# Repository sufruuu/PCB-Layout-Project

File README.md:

# PCB-Layout-Project
Submitted by T S Subramaniyan  
Final project submission on Schematic &amp; PCB Layout Designing.  
## Square Wave Generator using NE555 IC
Requirements:
- frequenchy = 1kHz
- Duty CYcle = 50%
- IC = NE555
- Used **Proteus** for circuit simulation
- Used **KiCAD V8.0.6** for Schematic Design and Layout Designing

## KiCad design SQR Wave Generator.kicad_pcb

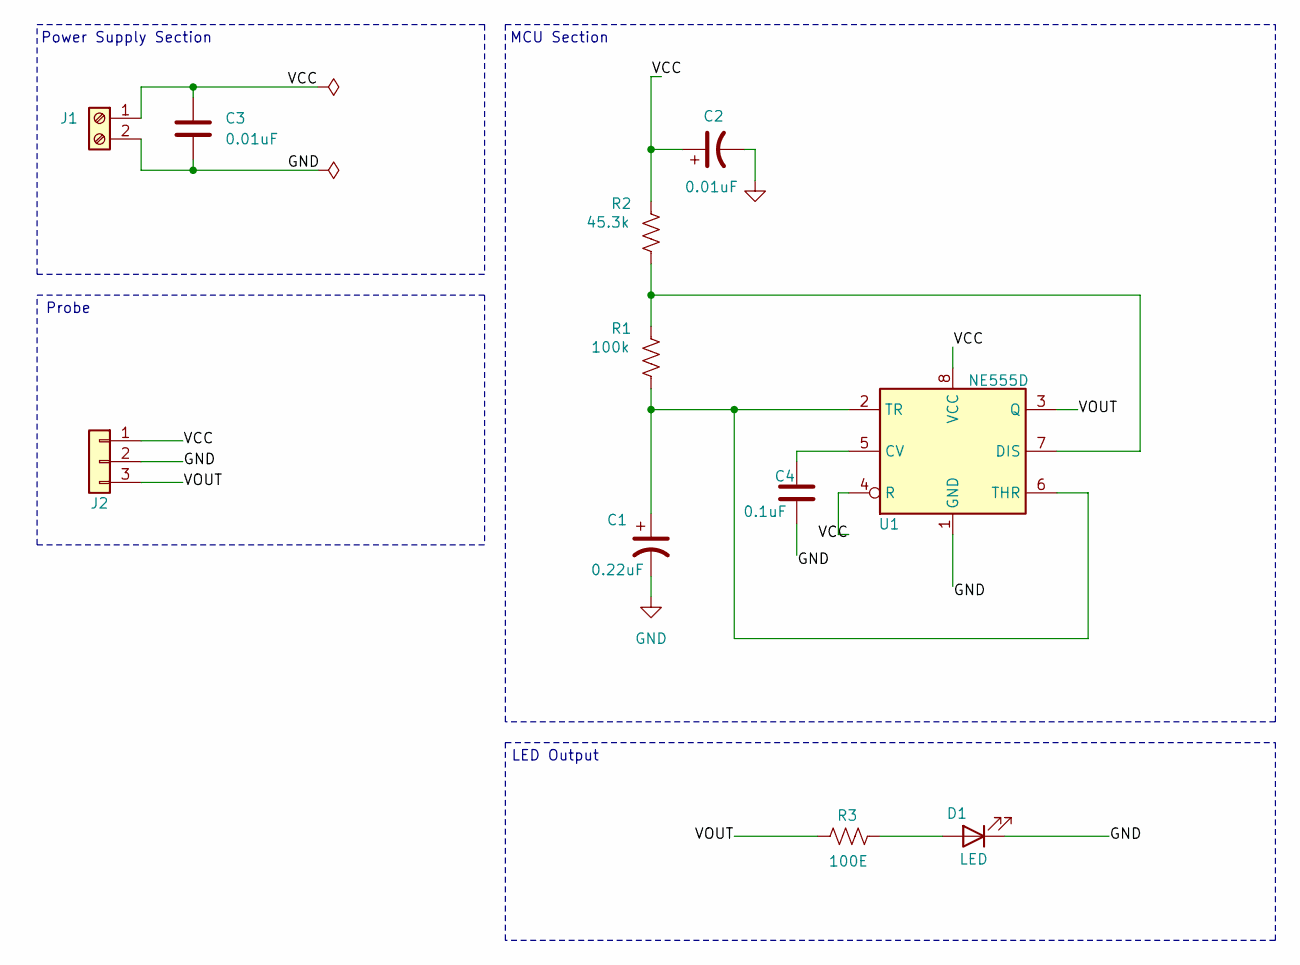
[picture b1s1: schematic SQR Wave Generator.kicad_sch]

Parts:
C1: 0.22uF; C_0805_2012Metric_Pad1.18x1.45mm_HandSolder
C2, C3: 0.01uF; C_0805_2012Metric_Pad1.18x1.45mm_HandSolder
C4: 0.1uF; C_0805_2012Metric_Pad1.18x1.45mm_HandSolder
D1: LED; LED_0805_2012Metric
J1: Screw_Terminal_01x02; TerminalBlock_Phoenix_MKDS-1,5-2-5.08_1x02_P5.08mm_Horizont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
J2: Conn_01x02; PinHeader_1x03_P2.54mm_Vertical
R1: 100k; R_0805_2012Metric
R2: 45.3k; R_0805_2012Metric
R3: 100E; R_0805_2012Metric
U1: NE555D; SOIC-8_3.9x4.9mm_P1.27mm

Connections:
/VCC: C2.1, C3.1, J1.1, J2.1, R2.1, U1.4 (R), U1.8 (VCC)
/VOUT: J2.3, R3.1, U1.3 (Q)
GND: C1.2, C2.2, C3.2, C4.2, D1.1 (K), J1.2, J2.2, U1.1 (GND)
unnamed: D1.2 (A), R3.2
unnamed: C4.1, U1.5 (CV)
unnamed: R1.1, R2.2, U1.7 (DIS)
unnamed: C1.1, R1.2, U1.2 (TR), U1.6 (THR)

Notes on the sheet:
MCU Section
LED Output
Probe
Power Supply Section

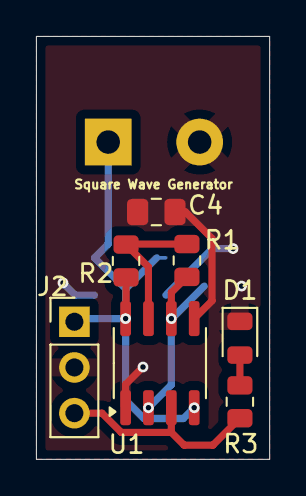
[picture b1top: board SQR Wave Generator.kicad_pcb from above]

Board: 2 copper layers, 13.0 x 23.5 mm, 11 parts (0 on the bottom side), 7 nets.

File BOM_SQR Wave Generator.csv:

"Reference","Value","Footprint","Qty"
"C1","0.22uF","Capacitor_SMD:C_0805_2012Metric_Pad1.18x1.45mm_HandSolder","1"
"C2,C3","0.01uF","Capacitor_SMD:C_0805_2012Metric_Pad1.18x1.45mm_HandSolder","2"
"D1","LED","LED_SMD:LED_0805_2012Metric","1"
"J1","Screw_Terminal_01x02","TerminalBlock_Phoenix:TerminalBlock_Phoenix_MKDS-1,5-2-5.08_1x02_P5.08mm_Horizontal","1"
"J2","Conn_01x02","Connector_PinHeader_2.54mm:PinHeader_1x03_P2.54mm_Vertical","1"
"R1","100k","Resistor_SMD:R_0805_2012Metric","1"
"R2","45.3k","Resistor_SMD:R_0805_2012Metric","1"
"R3","100E","Resistor_SMD:R_0805_2012Metric","1"
"U1","NE555D","Package_SO:SOIC-8_3.9x4.9mm_P1.27mm","1"

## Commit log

2024-12-25 Update README.md
    little about the project
2024-12-25 Schematic & Layout files
2024-12-25 Simulation Schematic
    Circuit done in Proteus for simulation
2024-12-25 Schematic PDF
